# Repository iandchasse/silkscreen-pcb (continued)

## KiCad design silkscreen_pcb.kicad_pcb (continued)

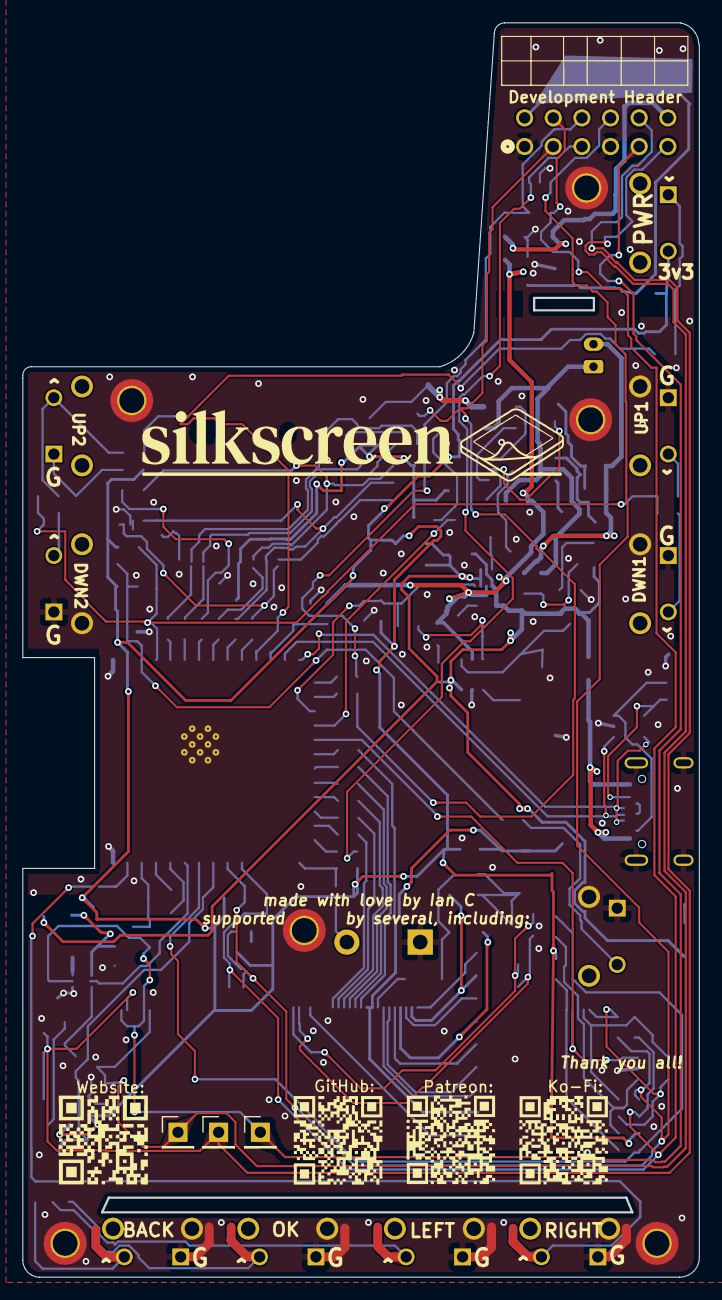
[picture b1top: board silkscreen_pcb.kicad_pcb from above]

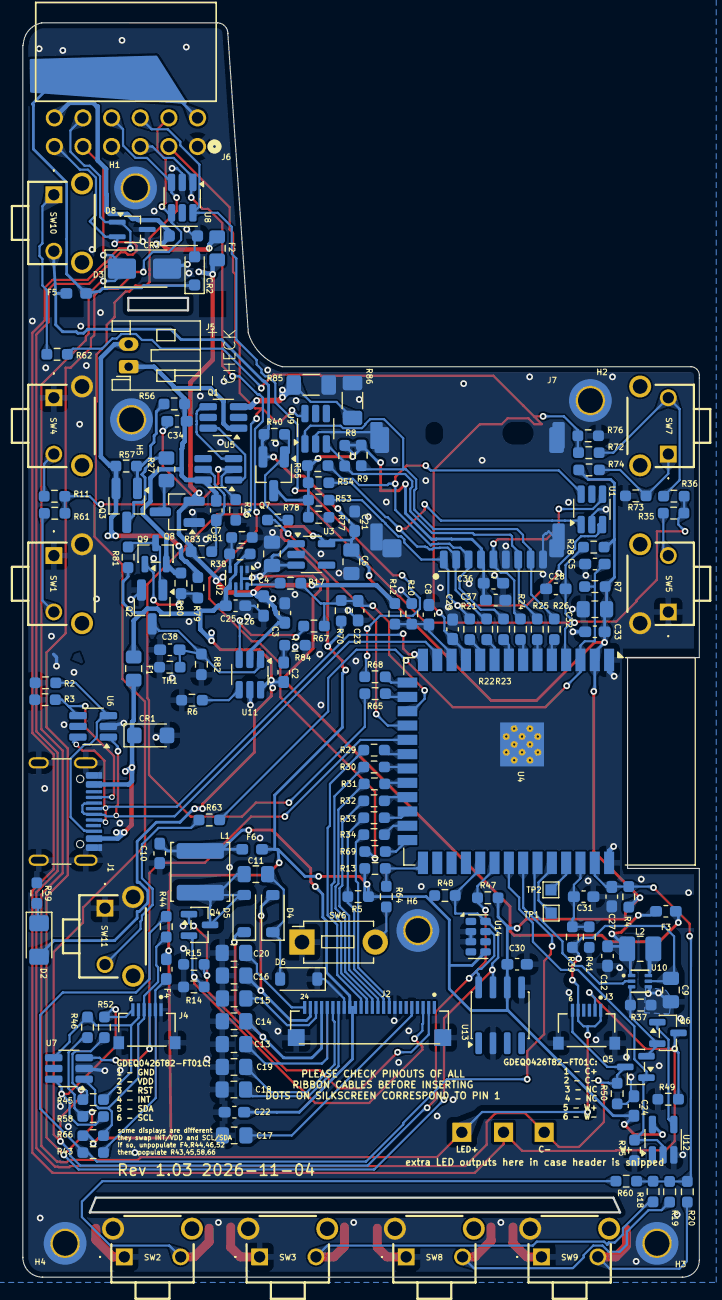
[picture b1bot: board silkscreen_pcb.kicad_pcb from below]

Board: 2 copper layers, 60.0 x 111.3 mm, 189 parts (185 on the bottom side), 116 nets.

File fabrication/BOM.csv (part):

Qty,Designators,Value,Footprint,Manufacturer,MPN,LCSC alt,Unit USD,Ext USD,Price src,DigiKey,DNP,Notes
1,U12,74LVC1G04,SOT-23-5_HandSoldering,Texas Instruments,SN74LVC1G04DBVR,,0.10,0.10,est,https://www.digikey.com/en/products/result?keywords=SN74LVC1G04DBVR,,inverter
1,U13,DS3231MZ,SOIC-8_3.9x4.9mm_P1.27mm,Analog Devices,DS3231MZ+,LCSC clone (e.g. C9866) far cheaper,5.50,5.50,est,https://www.digikey.com/en/products/result?keywords=DS3231MZ%2B,,RTC
1,U5,DW01A,SOT-23-6_Handsoldering,Fortune,DW01A,,0.10,0.10,ODS,https://www.digikey.com/en/products/result?keywords=DW01A,,LCSC C8724; source LCSC
1,U4,ESP32-S3-WROOM-1,ESP32-S3-WROOM-1,Espressif,ESP32-S3-WROOM-1-N16R8,N8R8 (less flash / cheaper),6.50,6.50,ODS,https://www.digikey.com/en/products/result?keywords=ESP32-S3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,JLC C2913202,16MB flash + 8MB octal PSRAM; must be an R8 (octal-PSRAM) part
1,U3,TLV75533PDBV,SOT-23-5_HandSoldering,Texas Instruments,TLV75533PDBVR,,0.35,0.35,est,https://www.digikey.com/en/products/result?keywords=TLV75533PDBVR,,3.3V LDO
1,U11,TP4056-42-ESOP8,SOIC-8-1EP_3.9x4.9mm_P1.27mm_EP2.41x3.3mm_ThermalVias,Nanjing Extension,TP4056-42-ESOP8,,0.15,0.15,est,https://www.digikey.com/en/products/result?keywords=TP4056-42-ESOP8,,LCSC C382139; source LCSC
5,U1 U6 U7 U8 U9,TPD4E1U06DBVR,SOT-23-6_Handsoldering,Texas Instruments,TPD4E1U06DBVR,,0.86,4.30,ODS,https://www.digikey.com/en/products/result?keywords=296-35965-1-ND,,
1,U2,TPS2116DRL,SOT-583-8,Texas Instruments,TPS2116DRL,,0.60,0.60,est,https://www.digikey.com/en/products/result?keywords=TPS2116DRL,,power-path mux
1,U10,TPS923610DRLR,U_DRL0006A_6L_TEX-M,Texas Instruments,TPS923610DRLR,,0.70,0.70,est,https://www.digikey.com/en/products/result?keywords=TPS923610DRLR,,frontlight boost
1,J5,Conn_01x02,JST_PH_S2B-PH-K_1x02_P2.00mm_Horizontal,JST,B2B-PH-K-S(LF)(SN),A2001WR-2P (LCSC PH equiv),0.15,0.15,est,https://www.digikey.com/en/products/result?keywords=B2B-PH-K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,,2p PH
1,J2,FH34SRJ-24S-0.5SH_50_,HRS_FH34SRJ-24S-0.5SH_50_,Hirose,FH34SRJ-24S-0.5SH(50),,2.26,2.26,ODS,https://www.digikey.com/en/products/result?keywords=FH34SRJ-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,,24p ZIF
2,J3 J4,FH34SRJ-6S-0.5SH_50_,HRS_FH34SRJ-6S-0.5SH_50_,Hirose,FH34SRJ-6S-0.5SH(50),,0.79,1.58,ODS,https://www.digikey.com/en/products/result?keywords=H125773CT-ND,,
1,J7,Micro_SD_Card,microSD_dualsource:microSD_PushPush_TFPUSH-MEM2075,GCT,MEM2075-00-140-01-A,TF PUSH (LCSC C393941 ~$0.06 for JLC),1.92,1.92,ODS,https://www.digikey.com/en/products/result?keywords=MEM2075-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,,push-push microSD; unified footprint (DigiKey=MEM2075, JLC=TF PUSH)
1,J6,PPPC062LJBN-RC,CONN_PPPC062LJBN-RC_SUL,Sullins,PPPC062LJBN-RC,"A2541HWR-2x6P (LCSC, if OOS)",1.50,1.50,est,https://www.digikey.com/en/products/result?keywords=PPPC062LJBN-RC,,2x6 header
1,J1,USB_C_Receptacle,USB_C_Receptacle_GCT_USB4085,GCT,USB4085-GF-A-060,,0.91,0.91,ODS,https://www.digikey.com/en/products/result?keywords=USB4085-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,,USB-C; verify suffix
3,Q3 Q7 Q8,AO3419,SOT-23_Handsoldering,Alpha & Omega,AO3419,IRLML6402,0.49,1.47,ODS,https://www.digikey.com/en/products/result?keywords=AO3419,,
3,Q4 Q5 Q6,BSS138,SOT-23,onsemi,BSS138LT1G,,0.31,0.93,ODS,https://www.digikey.com/en/products/result?keywords=BSS138LT1G,,
1,Q1,FS8205A,SOT-23-6_Handsoldering,Fortune,FS8205A,,0.39,0.39,ODS,https://www.digikey.com/en/products/result?keywords=FS8205A,,LCSC C32254
3,D4 D5 D6,B5819W,D_SOD-123,MCC,B5819W,,0.22,0.66,ODS,https://www.digikey.com/en/products/result?keywords=B5819W,,equiv 1N5819HW-7-F
1,D2,LED,LED_1206_3216Metric_Pad1.42x1.75mm_HandSolder,,LED 1206,,0.10,0.10,est,,,power indicator
1,D8,PESD2IVN-UX,SOT-323_SC-70_Handsoldering,Nexperia,PESD2IVN-UX,,0.20,0.20,est,https://www.digikey.com/en/products/result?keywords=PESD2IVN-UX,,ESD
1,D3,SMAJ26A,D_SMA,Littelfuse,SMAJ26A,,0.30,0.30,est,https://www.digikey.com/en/products/result?keywords=SMAJ26A,,TVS
3,CR1 CR2 CR3,TSD05CDYFR,D_SOD-323_HandSoldering,Texas Instruments,TSD05CDYFR,GOODWORK SD05C,0.67,2.01,ODS,https://www.digikey.com/en/products/result?keywords=TSD05CDYFR,,
1,L1,22u,IND_SRN3010C-100M,TDK,VLS3012HBX-220M,,0.50,0.50,est,https://www.digikey.com/en/products/result?keywords=VLS3012HBX-220M,,22uH shielded
1,L2,4.7u,L_1008_2520Metric_Pad1.43x2.20mm_HandSolder,TDK,VLS252010HBU-4R7M,,0.07,0.07,est,https://www.lcsc.com/product-detail/C413592.html,LCSC C413592,4.7uH metal-composite shielded 1008 (2.5x2.0x1.0mm) Isat 1.55A Irms 1.01A DCR 274m
1,F1,0805L100WR,Fuse_0805_2012Metric_Pad1.15x1.40mm_HandSolder,Littelfuse,0805L100WR,,0.30,0.30,est,https://www.digikey.com/en/products/result?keywords=0805L100WR,,1.0A PPTC
10,SW1 SW2 SW3 SW4 SW5 SW7 SW8 SW9 SW10 SW11,SW_Push,MJTP1117,APEM,MJTP1117,"TS365ZJ (LCSC C557598, ~$0.027, drop-in same 5.0x2.5 land) / SKHLLAA010",0.12,1.20,est,https://www.digikey.com/en/products/result?keywords=MJTP1117,,6mm right-angle tactile
1,SW6,SW_Push,SW_PUSH_1P1T_6x3.5mm_H4.3_APEM_MJTP1243,APEM,MJTP1243,TS365ZJ (if populating),0,0,DNP,https://www.digikey.com/en/products/result?keywords=MJTP1243,,DNP - 6x3.5mm side tactile not populated
6,R27 R42 R44 R46 R52 R73,0,R_0603_1608Metric_Pad0.98x0.95mm_HandSolder,,RES 0 0603,,0.10,0.60,ODS,https://www.digikey.com/en/products/result?keywords=RES%200%200603,,0 ohm jumper
5,R43 R45 R58 R66 R74,0,R_0603_1608Metric_Pad0.98x0.95mm_HandSolder,,RES 0 0603,,0.10,0.50,ODS,https://www.digikey.com/en/products/result?keywords=RES%200%200603,DNP,0 ohm jumper
4,R60 R61 R63 R64,100,R_0603_1608Metric_Pad0.98x0.95mm_HandSolder,,RES 100 0603,,0.10,0.40,ODS,https://www.digikey.com/en/products/result?keywords=RES%2010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,,
6,R40 R51 R70 R75 R76 R77,100k,R_0603_1608Metric_Pad0.98x0.95mm_HandSolder,,RES 100k 0603,,0.10,0.60,ODS,https://www.digikey.com/en/products/result?keywords=RES%2010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,,
13,R4 R5 R7 R8 R9 R13 R15 R28 R53 R54 R55 R56 R62,10k,R_0603_1608Metric_Pad0.98x0.95mm_HandSolder,,RES 10k 0603,,0.10,1.30,ODS,https://www.digikey.com/en/products/result?keywords=RES%2010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,,
1,R72,10k,R_0603_1608Metric_Pad0.98x0.95mm_HandSolder,,RES 10k 0603,,0.10,0.10,ODS,https://www.digikey.com/en/products/result?keywords=RES%2010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,DNP,
1,R41,120k,R_0603_1608Metric_Pad0.98x0.95mm_HandSolder,,RES 120k 0603,,0.10,0.10,ODS,https://www.digikey.com/en/products/result?keywords=RES%2012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,,
1,R11,12k,R_0603_1608Metric_Pad0.98x0.95mm_HandSolder,,RES 12k 0603,,0.10,0.10,ODS,https://www.digikey.com/en/products/result?keywords=RES%2012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,,
1,R37,13.3,R_0603_1608Metric_Pad0.98x0.95mm_HandSolder,,RES 13.3 0603,,0.10,0.10,ODS,https://www.digikey.com/en/products/result?keywords=RES%2013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,,
1,R17,150k,R_0603_1608Metric_Pad0.98x0.95mm_HandSolder,,RES 150k 0603,,0.10,0.10,ODS,https://www.digikey.com/en/products/result?keywords=RES%2015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,,
7,R1 R10 R12 R39 R49 R50 R57,1M,R_0603_1608Metric_Pad0.98x0.95mm_HandSolder,,RES 1M 0603,,0.10,0.70,ODS,https://www.digikey.com/en/products/result?keywords=RES%201M%200603,,
2,R16 R78,1k,R_0603_1608Metric_Pad0.98x0.95mm_HandSolder,,RES 1k 0603,,0.10,0.20,ODS,https://www.digikey.com/en/products/result?keywords=RES%201k%200603,,
2,R47 R48,2.2k,R_0603_1608Metric_Pad0.98x0.95mm_HandSolder,,RES 2.2k 0603,,0.10,0.20,ODS,https://www.digikey.com/en/products/result?keywords=RES%202.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,,
1,R19,20k,R_0603_1608Metric_Pad0.98x0.95mm_HandSolder,,RES 20k 0603,,0.10,0.10,ODS,https://www.digikey.com/en/products/result?keywords=RES%2020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,,
1,R71,22k,R_0603_1608Metric_Pad0.98x0.95mm_HandSolder,,RES 22k 0603,,0.10,0.10,ODS,https://www.digikey.com/en/products/result?keywords=RES%2022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,,
1,R59,2k,R_0603_1608Metric_Pad0.98x0.95mm_HandSolder,,RES 2k 0603,,0.10,0.10,ODS,https://www.digikey.com/en/products/result?keywords=RES%202k%200603,,
1,R14,3,R_0603_1608Metric_Pad0.98x0.95mm_HandSolder,,RES 3 0603,,0.10,0.10,ODS,https://www.digikey.com/en/products/result?keywords=RES%203%200603,,
1,R38,300k,R_0603_1608Metric_Pad0.98x0.95mm_HandSolder,,RES 300k 0603,,0.10,0.10,ODS,https://www.digikey.com/en/products/result?keywords=RES%2030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,,
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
